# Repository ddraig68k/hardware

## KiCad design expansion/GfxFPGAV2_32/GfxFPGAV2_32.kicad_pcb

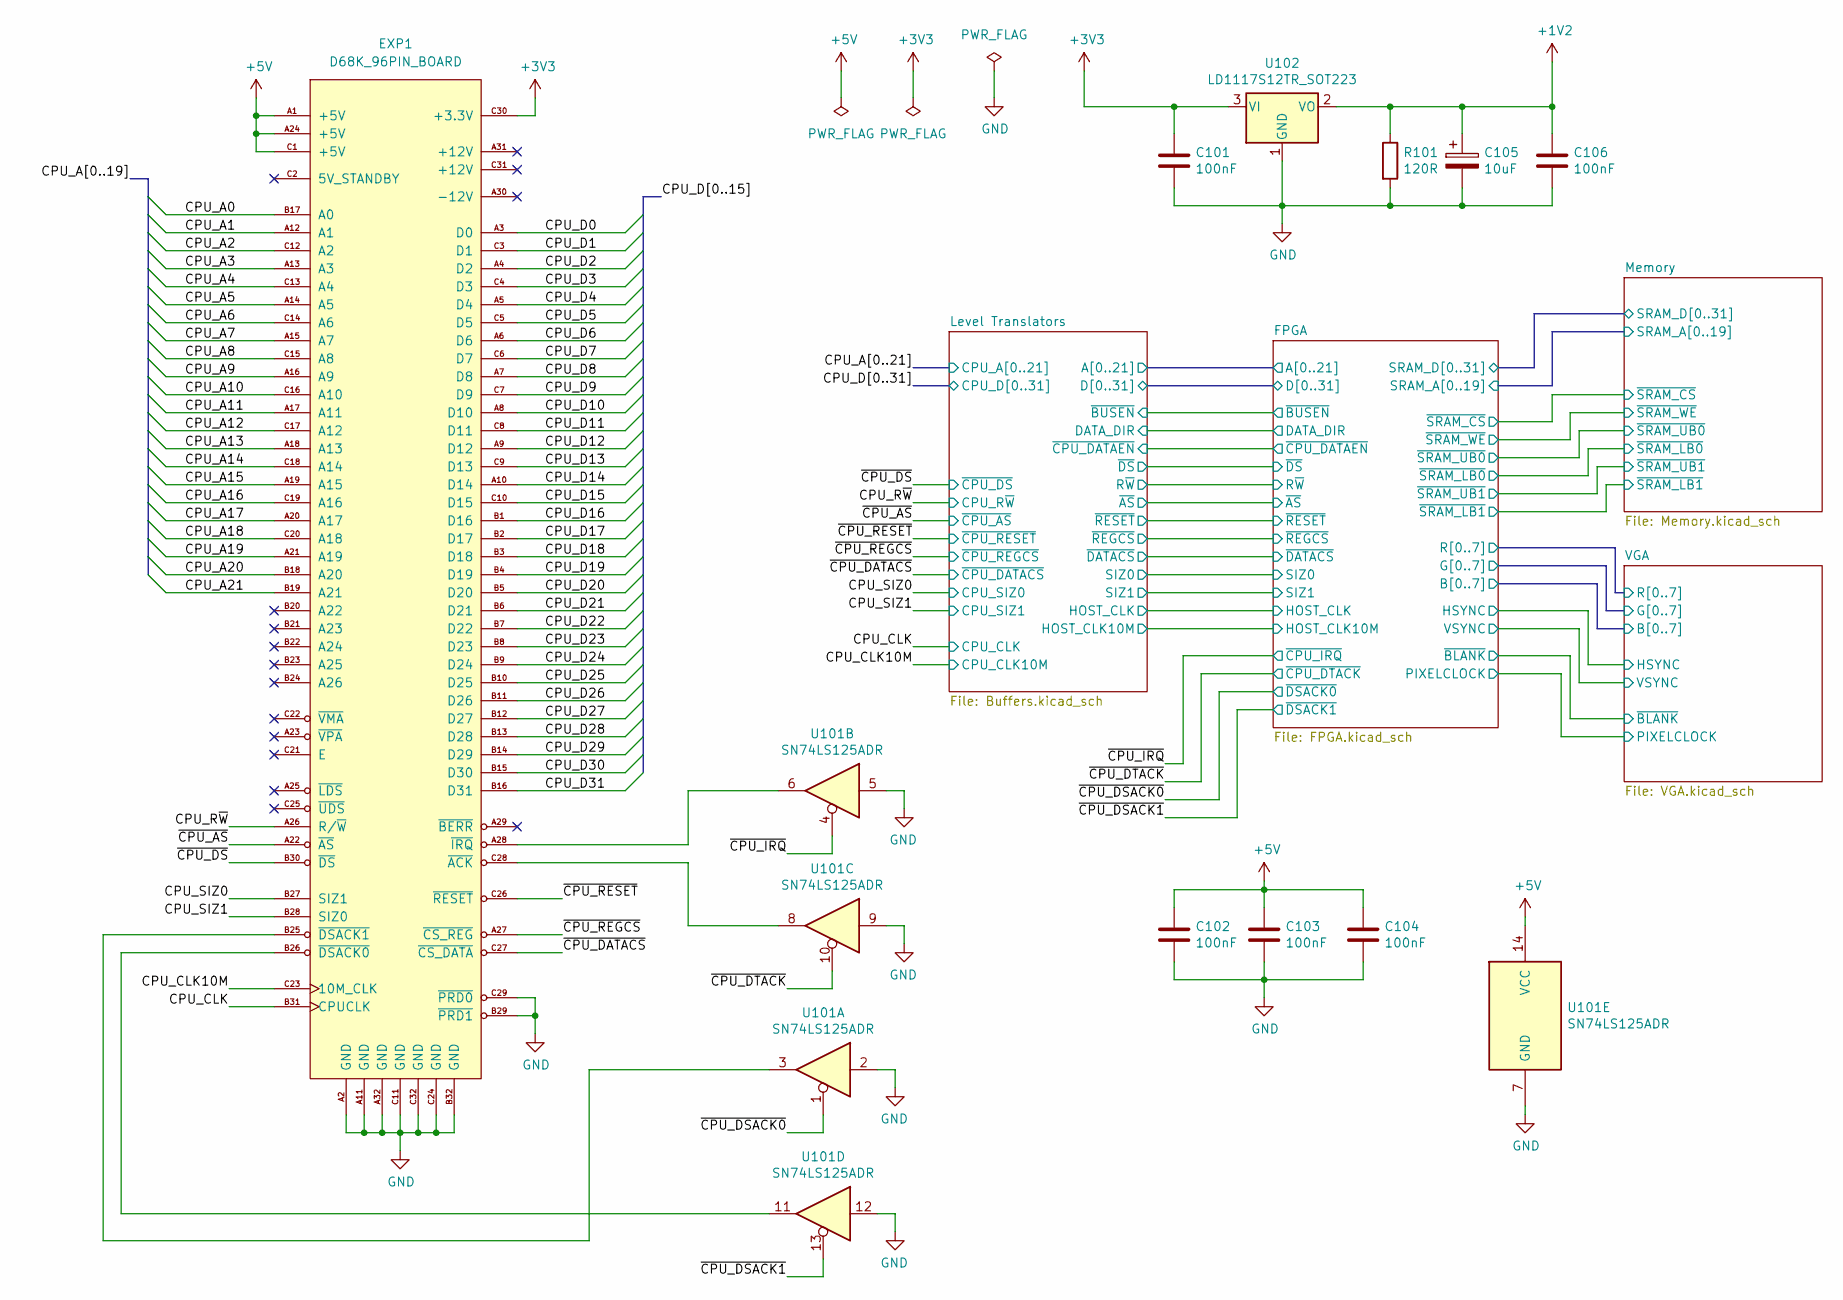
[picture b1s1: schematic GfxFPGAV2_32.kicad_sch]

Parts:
C101, C102, C103, C104, C106: 100nF; C_0805_2012Metric
C105: 10uF; CP_Elec_4x5.3
EXP1: D68K_96PIN_BOARD; DIN41612_C_3x32_Male_Horizontal_THT
R101: 120R; R_0805_2012Metric
U101: SN74LS125ADR; SO-14_3.9x8.65mm_P1.27mm
U102: LD1117S12TR_SOT223; SOT-223-3_TabPin2

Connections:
+1V2: C105.1, C106.1, R101.1, U102.2 (VO); also elsewhere on the board
+3V3: C101.1, EXP1.C30 (+3.3V), U102.3 (VI); also elsewhere on the board
+5V: C102.1, C103.1, C104.1, EXP1.A1 (+5V), EXP1.A24 (+5V), EXP1.C1 (+5V), U101.14 (VCC); also elsewhere on the board
/CPU_A0: EXP1.B17 (A0); also elsewhere on the board
/CPU_A1: EXP1.A12 (A1); also elsewhere on the board
/CPU_A2: EXP1.C12 (A2); also elsewhere on the board
/CPU_A3: EXP1.A13 (A3); also elsewhere on the board
/CPU_A4: EXP1.C13 (A4); also elsewhere on the board
/CPU_A5: EXP1.A14 (A5); also elsewhere on the board
/CPU_A6: EXP1.C14 (A6); also elsewhere on the board
/CPU_A7: EXP1.A15 (A7); also elsewhere on the board
/CPU_A8: EXP1.C15 (A8); also elsewhere on the board
/CPU_A9: EXP1.A16 (A9); also elsewhere on the board
/CPU_A10: EXP1.C16 (A10); also elsewhere on the board
/CPU_A11: EXP1.A17 (A11); also elsewhere on the board
/CPU_A12: EXP1.C17 (A12); also elsewhere on the board
/CPU_A13: EXP1.A18 (A13); also elsewhere on the board
/CPU_A14: EXP1.C18 (A14); also elsewhere on the board
/CPU_A15: EXP1.A19 (A15); also elsewhere on the board
/CPU_A16: EXP1.C19 (A16); also elsewhere on the board
/CPU_A17: EXP1.A20 (A17); also elsewhere on the board
/CPU_A18: EXP1.C20 (A18); also elsewhere on the board
/CPU_A19: EXP1.A21 (A19); also elsewhere on the board
/CPU_A20: EXP1.B18 (A20); also elsewhere on the board
/CPU_A21: EXP1.B19 (A21); also elsewhere on the board
/CPU_CLK: EXP1.B31 (CPUCLK); also elsewhere on the board
/CPU_CLK10M: EXP1.C23 (10M_CLK); also elsewhere on the board
/CPU_D0: EXP1.A3 (D0); also elsewhere on the board
/CPU_D1: EXP1.C3 (D1); also elsewhere on the board
/CPU_D2: EXP1.A4 (D2); also elsewhere on the board
/CPU_D3: EXP1.C4 (D3); also elsewhere on the board
/CPU_D4: EXP1.A5 (D4); also elsewhere on the board
/CPU_D5: EXP1.C5 (D5); also elsewhere on the board
/CPU_D6: EXP1.A6 (D6); also elsewhere on the board
/CPU_D7: EXP1.C6 (D7); also elsewhere on the board
/CPU_D8: EXP1.A7 (D8); also elsewhere on the board
/CPU_D9: EXP1.C7 (D9); also elsewhere on the board
/CPU_D10: EXP1.A8 (D10); also elsewhere on the board
/CPU_D11: EXP1.C8 (D11); also elsewhere on the board
/CPU_D12: EXP1.A9 (D12); also elsewhere on the board
/CPU_D13: EXP1.C9 (D13); also elsewhere on the board
/CPU_D14: EXP1.A10 (D14); also elsewhere on the board
/CPU_D15: EXP1.C10 (D15); also elsewhere on the board
/CPU_D16: EXP1.B1 (D16); also elsewhere on the board
/CPU_D17: EXP1.B2 (D17); also elsewhere on the board
/CPU_D18: EXP1.B3 (D18); also elsewhere on the board
/CPU_D19: EXP1.B4 (D19); also elsewhere on the board
/CPU_D20: EXP1.B5 (D20); also elsewhere on the board
/CPU_D21: EXP1.B6 (D21); also elsewhere on the board
/CPU_D22: EXP1.B7 (D22); also elsewhere on the board
/CPU_D23: EXP1.B8 (D23); also elsewhere on the board
/CPU_D24: EXP1.B9 (D24); also elsewhere on the board
/CPU_D25: EXP1.B10 (D25); also elsewhere on the board
/CPU_D26: EXP1.B11 (D26); also elsewhere on the board
/CPU_D27: EXP1.B12 (D27); also elsewhere on the board
/CPU_D28: EXP1.B13 (D28); also elsewhere on the board
/CPU_D29: EXP1.B14 (D29); also elsewhere on the board
/CPU_D30: EXP1.B15 (D30); also elsewhere on the board
/CPU_D31: EXP1.B16 (D31); also elsewhere on the board
/CPU_R~W: EXP1.A26 (R/~W); also elsewhere on the board
/CPU_SIZ0: EXP1.B27 (SIZ1); also elsewhere on the board
/CPU_SIZ1: EXP1.B28 (SIZ0); also elsewhere on the board
/~CPU_AS: EXP1.A22 (~AS); also elsewhere on the board
/~CPU_DATACS: EXP1.C27 (~CS_DATA); also elsewhere on the board
/~CPU_DSACK0: U101.1; also elsewhere on the board
/~CPU_DSACK1: U101.13; also elsewhere on the board
/~CPU_DS: EXP1.B30 (~DS); also elsewhere on the board
/~CPU_DTACK: U101.10; also elsewhere on the board
/~CPU_IRQ: U101.4; also elsewhere on the board
/~CPU_REGCS: EXP1.A27 (~CS_REG); also elsewhere on the board
/~CPU_RESET: EXP1.C26 (~RESET); also elsewhere on the board
GND: C101.2, C102.2, C103.2, C104.2, C105.2, C106.2, EXP1.A2 (GND), EXP1.A11 (GND), EXP1.A32 (GND), EXP1.B29 (~PRD1), EXP1.B32 (GND), EXP1.C11 (GND), EXP1.C24 (GND), EXP1.C29 (~PRD0), EXP1.C32 (GND), R101.2, U101.2, U101.5, U101.7 (GND), U101.9, U101.12, U102.1 (GND); also elsewhere on the board
unnamed: EXP1.C28 (~ACK), U101.8
unnamed: EXP1.B26 (~DSACK0), U101.11
unnamed: EXP1.B25 (~DSACK1), U101.3
unnamed: EXP1.A28 (~IRQ), U101.6

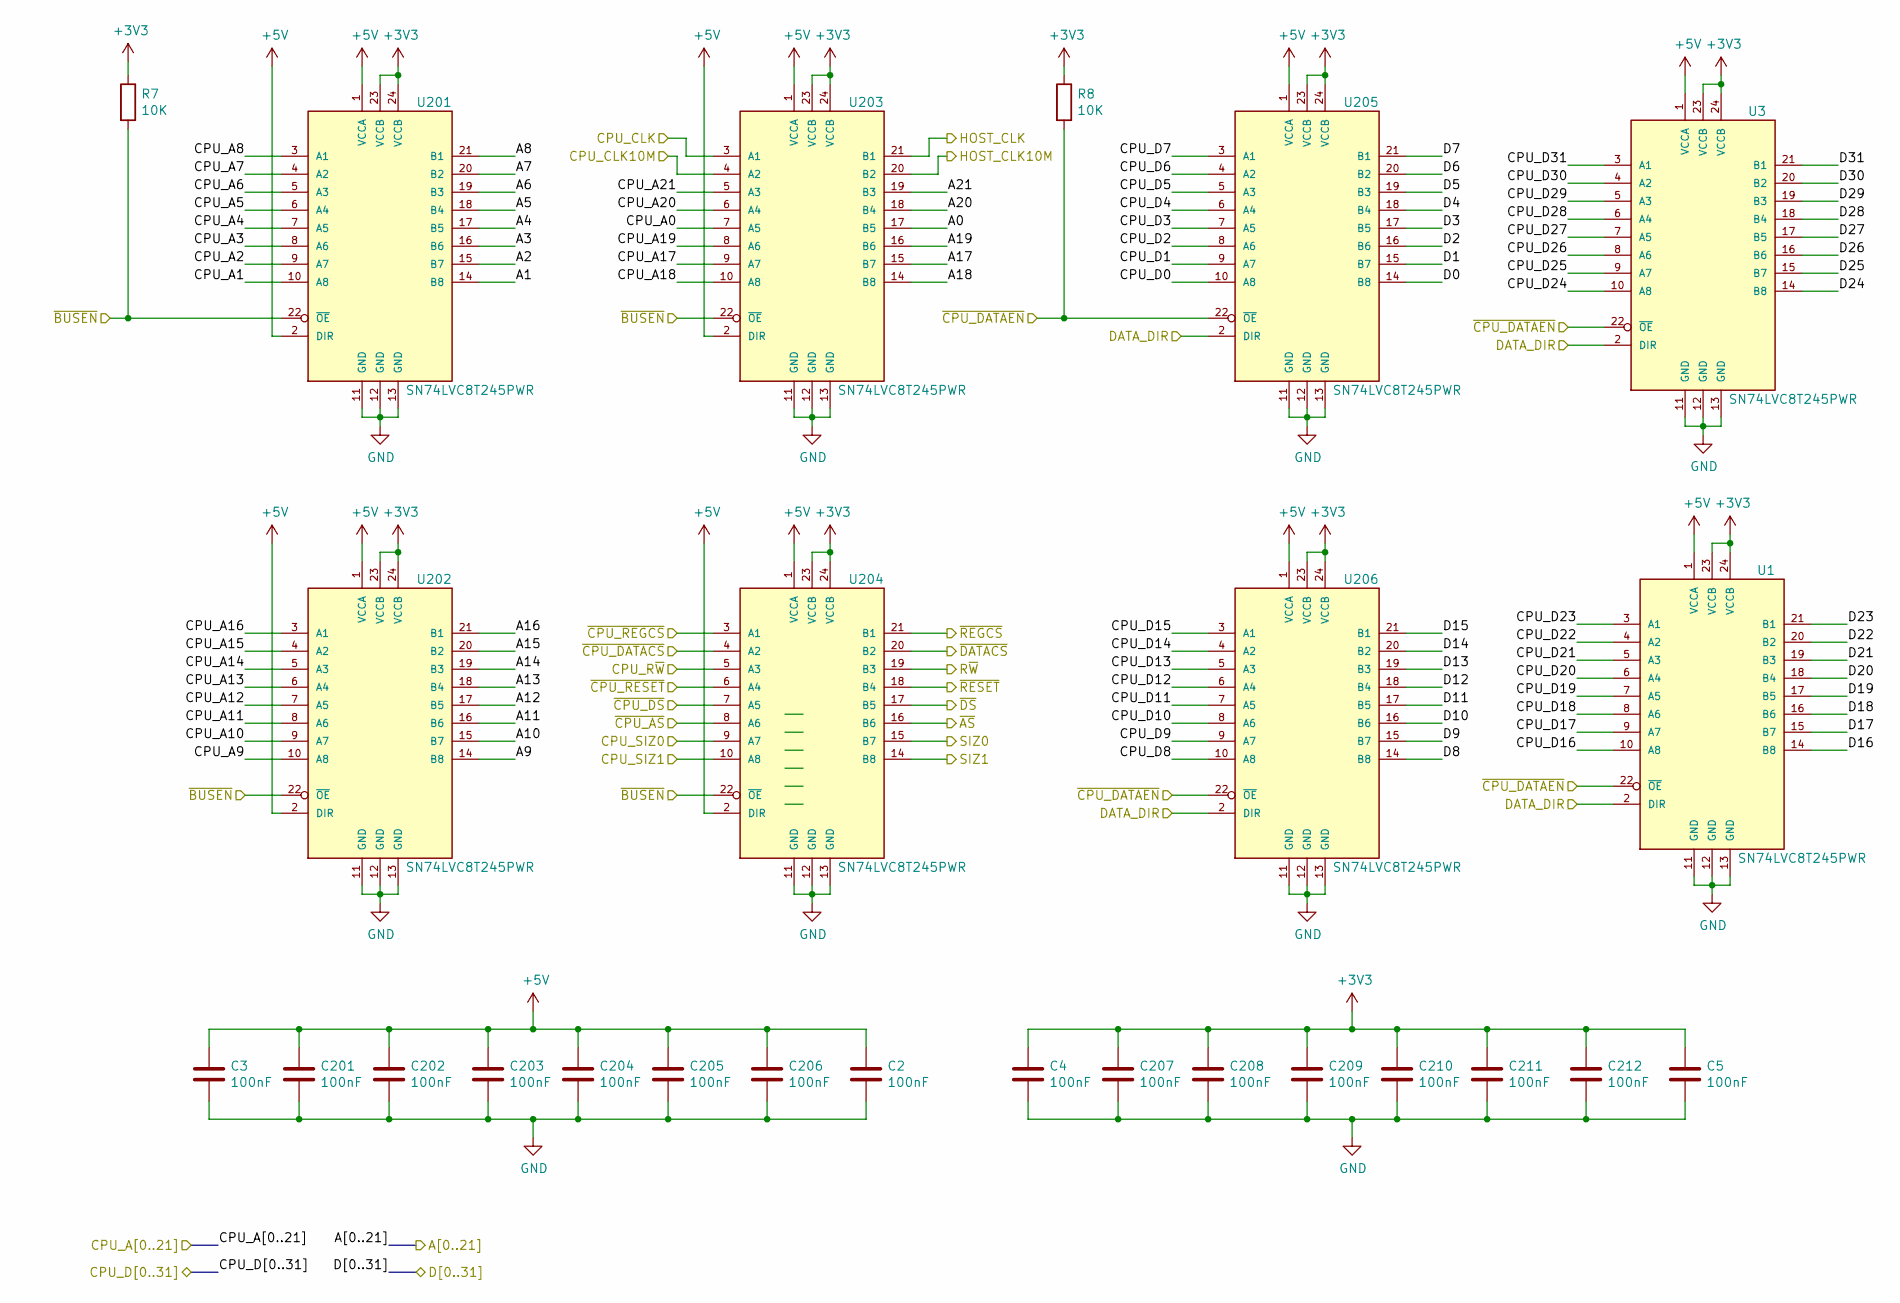
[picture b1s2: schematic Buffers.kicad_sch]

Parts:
C2, C3, C4, C5, C201, C202, C203, C204, C205, C206, C207, C208, C209, C210, C211, C212: 100nF; C_0805_2012Metric
R7, R8: 10K; R_0805_2012Metric
U1, U3, U201, U202, U203, U204, U205, U206: SN74LVC8T245PWR; SOP65P640X120-24N

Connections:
+3V3: C4.1, C5.1, C207.1, C208.1, C209.1, C210.1, C211.1, C212.1, R7.1, R8.1, U1.23 (VCCB), U1.24 (VCCB), U3.23 (VCCB), U3.24 (VCCB), U201.23 (VCCB), U201.24 (VCCB), U202.23 (VCCB), U202.24 (VCCB), U203.23 (VCCB), U203.24 (VCCB), U204.23 (VCCB), U204.24 (VCCB), U205.23 (VCCB), U205.24 (VCCB), U206.23 (VCCB), U206.24 (VCCB); also elsewhere on the board
+5V: C2.1, C3.1, C201.1, C202.1, C203.1, C204.1, C205.1, C206.1, U1.1 (VCCA), U3.1 (VCCA), U201.1 (VCCA), U201.2 (DIR), U202.1 (VCCA), U202.2 (DIR), U203.1 (VCCA), U203.2 (DIR), U204.1 (VCCA), U204.2 (DIR), U205.1 (VCCA), U206.1 (VCCA); also elsewhere on the board
/CPU_A0: U203.7 (A5); also elsewhere on the board
/CPU_A1: U201.10 (A8); also elsewhere on the board
/CPU_A2: U201.9 (A7); also elsewhere on the board
/CPU_A3: U201.8 (A6); also elsewhere on the board
/CPU_A4: U201.7 (A5); also elsewhere on the board
/CPU_A5: U201.6 (A4); also elsewhere on the board
/CPU_A6: U201.5 (A3); also elsewhere on the board
/CPU_A7: U201.4 (A2); also elsewhere on the board
/CPU_A8: U201.3 (A1); also elsewhere on the board
/CPU_A9: U202.10 (A8); also elsewhere on the board
/CPU_A10: U202.9 (A7); also elsewhere on the board
/CPU_A11: U202.8 (A6); also elsewhere on the board
/CPU_A12: U202.7 (A5); also elsewhere on the board
/CPU_A13: U202.6 (A4); also elsewhere on the board
/CPU_A14: U202.5 (A3); also elsewhere on the board
/CPU_A15: U202.4 (A2); also elsewhere on the board
/CPU_A16: U202.3 (A1); also elsewhere on the board
/CPU_A17: U203.9 (A7); also elsewhere on the board
/CPU_A18: U203.10 (A8); also elsewhere on the board
/CPU_A19: U203.8 (A6); also elsewhere on the board
/CPU_A20: U203.6 (A4); also elsewhere on the board
/CPU_A21: U203.5 (A3); also elsewhere on the board
/CPU_CLK: U203.3 (A1); also elsewhere on the board
/CPU_CLK10M: U203.4 (A2); also elsewhere on the board
/CPU_D0: U205.10 (A8); also elsewhere on the board
/CPU_D1: U205.9 (A7); also elsewhere on the board
/CPU_D2: U205.8 (A6); also elsewhere on the board
/CPU_D3: U205.7 (A5); also elsewhere on the board
/CPU_D4: U205.6 (A4); also elsewhere on the board
/CPU_D5: U205.5 (A3); also elsewhere on the board
/CPU_D6: U205.4 (A2); also elsewhere on the board
/CPU_D7: U205.3 (A1); also elsewhere on the board
/CPU_D8: U206.10 (A8); also elsewhere on the board
/CPU_D9: U206.9 (A7); also elsewhere on the board
/CPU_D10: U206.8 (A6); also elsewhere on the board
/CPU_D11: U206.7 (A5); also elsewhere on the board
/CPU_D12: U206.6 (A4); also elsewhere on the board
/CPU_D13: U206.5 (A3); also elsewhere on the board
/CPU_D14: U206.4 (A2); also elsewhere on the board
/CPU_D15: U206.3 (A1); also elsewhere on the board
/CPU_D16: U1.10 (A8); also elsewhere on the board
/CPU_D17: U1.9 (A7); also elsewhere on the board
/CPU_D18: U1.8 (A6); also elsewhere on the board
/CPU_D19: U1.7 (A5); also elsewhere on the board
/CPU_D20: U1.6 (A4); also elsewhere on the board
/CPU_D21: U1.5 (A3); also elsewhere on the board
/CPU_D22: U1.4 (A2); also elsewhere on the board
/CPU_D23: U1.3 (A1); also elsewhere on the board
/CPU_D24: U3.10 (A8); also elsewhere on the board
/CPU_D25: U3.9 (A7); also elsewhere on the board
/CPU_D26: U3.8 (A6); also elsewhere on the board
/CPU_D27: U3.7 (A5); also elsewhere on the board
/CPU_D28: U3.6 (A4); also elsewhere on the board
/CPU_D29: U3.5 (A3); also elsewhere on the board
/CPU_D30: U3.4 (A2); also elsewhere on the board
/CPU_D31: U3.3 (A1); also elsewhere on the board
/CPU_R~W: U204.5 (A3); also elsewhere on the board
/CPU_SIZ0: U204.9 (A7); also elsewhere on the board
/CPU_SIZ1: U204.10 (A8); also elsewhere on the board
/FPGA/A0: U203.17 (B5); also elsewhere on the board
/FPGA/A1: U201.14 (B8); also elsewhere on the board
/FPGA/A2: U201.15 (B7); also elsewhere on the board
/FPGA/A3: U201.16 (B6); also elsewhere on the board
/FPGA/A4: U201.17 (B5); also elsewhere on the board
/FPGA/A5: U201.18 (B4); also elsewhere on the board
/FPGA/A6: U201.19 (B3); also elsewhere on the board
/FPGA/A7: U201.20 (B2); also elsewhere on the board
/FPGA/A8: U201.21 (B1); also elsewhere on the board
/FPGA/A9: U202.14 (B8); also elsewhere on the board
/FPGA/A10: U202.15 (B7); also elsewhere on the board
/FPGA/A11: U202.16 (B6); also elsewhere on the board
/FPGA/A12: U202.17 (B5); also elsewhere on the board
/FPGA/A13: U202.18 (B4); also elsewhere on the board
/FPGA/A14: U202.19 (B3); also elsewhere on the board
/FPGA/A15: U202.20 (B2); also elsewhere on the board
/FPGA/A16: U202.21 (B1); also elsewhere on the board
/FPGA/A17: U203.15 (B7); also elsewhere on the board
/FPGA/A18: U203.14 (B8); also elsewhere on the board
/FPGA/A19: U203.16 (B6); also elsewhere on the board
/FPGA/A20: U203.18 (B4); also elsewhere on the board
/FPGA/A21: U203.19 (B3); also elsewhere on the board
/FPGA/D0: U205.14 (B8); also elsewhere on the board
/FPGA/D1: U205.15 (B7); also elsewhere on the board
/FPGA/D2: U205.16 (B6); also elsewhere on the board
/FPGA/D3: U205.17 (B5); also elsewhere on the board
/FPGA/D4: U205.18 (B4); also elsewhere on the board
/FPGA/D5: U205.19 (B3); also elsewhere on the board
/FPGA/D6: U205.20 (B2); also elsewhere on the board
/FPGA/D7: U205.21 (B1); also elsewhere on the board
/FPGA/D8: U206.14 (B8); also elsewhere on the board
/FPGA/D9: U206.15 (B7); also elsewhere on the board
/FPGA/D10: U206.16 (B6); also elsewhere on the board
/FPGA/D11: U206.17 (B5); also elsewhere on the board
/FPGA/D12: U206.18 (B4); also elsewhere on the board
/FPGA/D13: U206.19 (B3); also elsewhere on the board
/FPGA/D14: U206.20 (B2); also elsewhere on the board
/FPGA/D15: U206.21 (B1); also elsewhere on the board
/FPGA/D16: U1.14 (B8); also elsewhere on the board
/FPGA/D17: U1.15 (B7); also elsewhere on the board
/FPGA/D18: U1.16 (B6); also elsewhere on the board
/FPGA/D19: U1.17 (B5); also elsewhere on the board
/FPGA/D20: U1.18 (B4); also elsewhere on the board
/FPGA/D21: U1.19 (B3); also elsewhere on the board
/FPGA/D22: U1.20 (B2); also elsewhere on the board
/FPGA/D23: U1.21 (B1); also elsewhere on the board
/FPGA/D24: U3.14 (B8); also elsewhere on the board
/FPGA/D25: U3.15 (B7); also elsewhere on the board
/FPGA/D26: U3.16 (B6); also elsewhere on the board
/FPGA/D27: U3.17 (B5); also elsewhere on the board
/FPGA/D28: U3.18 (B4); also elsewhere on the board
/FPGA/D29: U3.19 (B3); also elsewhere on the board
/FPGA/D30: U3.20 (B2); also elsewhere on the board
/FPGA/D31: U3.21 (B1); also elsewhere on the board
/FPGA/DATA_DIR: U1.2 (DIR), U3.2 (DIR), U205.2 (DIR), U206.2 (DIR); also elsewhere on the board
/FPGA/HOST_CLK: U203.21 (B1); also elsewhere on the board
/FPGA/HOST_CLK10M: U203.20 (B2); also elsewhere on the board
/FPGA/R~W: U204.19 (B3); also elsewhere on the board
/FPGA/SIZ0: U204.15 (B7); also elsewhere on the board
/FPGA/SIZ1: U204.14 (B8); also elsewhere on the board
/FPGA/~AS: U204.16 (B6); also elsewhere on the board
/FPGA/~BUSEN: R7.2, U201.22 (~OE), U202.22 (~OE), U203.22 (~OE), U204.22 (~OE); also elsewhere on the board
/FPGA/~CPU_DATAEN: R8.2, U1.22 (~OE), U3.22 (~OE), U205.22 (~OE), U206.22 (~OE); also elsewhere on the board
/FPGA/~DATACS: U204.20 (B2); also elsewhere on the board
/FPGA/~DS: U204.17 (B5); also elsewhere on the board
/FPGA/~REGCS: U204.21 (B1); also elsewhere on the board
/FPGA/~RESET: U204.18 (B4); also elsewhere on the board
/~CPU_AS: U204.8 (A6); also elsewhere on the board
/~CPU_DATACS: U204.4 (A2); also elsewhere on the board
/~CPU_DS: U204.7 (A5); also elsewhere on the board
/~CPU_REGCS: U204.3 (A1); also elsewhere on the board
/~CPU_RESET: U204.6 (A4); also elsewhere on the board
GND: C2.2, C3.2, C4.2, C5.2, C201.2, C202.2, C203.2, C204.2, C205.2, C206.2, C207.2, C208.2, C209.2, C210.2, C211.2, C212.2, U1.11 (GND), U1.12 (GND), U1.13 (GND), U3.11 (GND), U3.12 (GND), U3.13 (GND), U201.11 (GND), U201.12 (GND), U201.13 (GND), U202.11 (GND), U202.12 (GND), U202.13 (GND), U203.11 (GND), U203.12 (GND), U203.13 (GND), U204.11 (GND), U204.12 (GND), U204.13 (GND), U205.11 (GND), U205.12 (GND), U205.13 (GND), U206.11 (GND), U206.12 (GND), U206.13 (GND); also elsewhere on the board

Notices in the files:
expansion/GfxV9990/GfxV9990.kicad_pcb:
© 2021 Stephen Moody
yddraig09/yddraig09.kicad_pcb:
Y Ddraig Fach ©2024 Stephen Moody - https://ddraig68k.com
